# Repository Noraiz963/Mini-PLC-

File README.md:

# STM32 Mini PLC v1.0

A compact industrial-style PLC board designed in KiCad, built around an **STM32F407** microcontroller. It provides **8 optically isolated digital inputs**, **8 relay outputs**, **RS-485** communication and **USB-C** serial/bootloader access, all powered from **24 VDC**.

> **Status:** Hardware design v1.0 complete. The board has not been manufactured or tested, and no firmware has been written yet.

---

## Table of contents

- [Key features](#key-features)
- [Board gallery](#board-gallery)
- [Specifications](#specifications)
- [System overview](#system-overview)
- [Sub-systems](#sub-systems)
- [Connectors](#connectors)
- [PCB design](#pcb-design)
- [Repository structure](#repository-structure)
- [Project status and roadmap](#project-status-and-roadmap)
- [Tools](#tools)
- [License and credits](#license-and-credits)

---

## Key features

- STM32F407 microcontroller as the processing core
- 8 optically isolated digital inputs (optocoupler per channel)
- 8 relay outputs, MOSFET-driven, with freewheeling diodes
- RS-485 interface on a DB9 connector (suitable for Modbus RTU)
- USB-C with CH340C USB-to-UART bridge for serial debugging and bootloader flashing
- 5-pin SWD header for ST-LINK programming and debugging
- 24 VDC industrial supply with fuse and reverse-polarity protection
- Status LEDs on inputs and outputs
- Reset button

---

## Board gallery

### 3D render: top angle

### 3D render: side view

### 3D render: back side
Back side showing input labels (X1 to X8), copper routing and relay output pads.

### PCB layout (KiCad PCB editor)
Red traces are the top copper layer and blue traces are the bottom copper layer. The logic section (power, STM32, inputs, communication) is at the top, and the relay and output section is at the bottom.

---

## Specifications

| Parameter | Value |
|---|---|
| Microcontroller | STM32F407 |
| Supply input | 24 VDC |
| Digital inputs | 8, optically isolated |
| Relay outputs | 8, rated 250 VAC / 30 VDC, 5 A (per board silkscreen) |
| Communication | RS-485 (DB9 connector), USB-C (UART bridge) |
| Programming / debug | 5-pin SWD header for ST-LINK |
| Design tool | KiCad |
| Board layers | 2 (top and bottom copper) |
| Version | v1.0 |

---

## System overview

```mermaid
flowchart LR
    PWR[24 VDC input<br/>J1, F1, D1] --> BUCK[Buck converter U1]
    BUCK --> LDO[3.3 V regulator U2]
    LDO --> MCU[STM32F407<br/>U13]
    IN[Field inputs X1-X8<br/>J2] --> OPTO[Optocouplers<br/>U4-U11]
    OPTO --> MCU
    MCU --> FET[MOSFET drivers<br/>Q2-Q9]
    FET --> RLY[Relays K2-K9]
    RLY --> OUT[Outputs Y1-Y8<br/>J3]
    MCU <--> RS[RS-485 transceiver U12<br/>DB9 J4]
    MCU <--> USB[CH340C U14<br/>USB-C J19]
    MCU <--> SWD[SWD header J5]
```

---

## Sub-systems

| Sub-system | Key components | Description |
|---|---|---|
| Power stage | J1, F1, D1, U1, U2 | Accepts 24 VDC industrial input, protected by a fuse and a reverse-polarity diode. A switching buck converter (U1) and a 3.3 V linear regulator (U2) power the logic. |
| Processing core | U13 (STM32F407), C9 to C11 | Main microcontroller for application logic, with decoupling capacitors for stability. |
| Programming and debug | J5 (3V3, SWDIO, RST, SWCLK, GND) | 5-pin header for debugging and flashing with an external ST-LINK. Pin 1 is the 3.3 V reference (VTREF). |
| USB and serial | J19 (USB-C), U14 (CH340C) | USB-to-UART bridge for serial monitoring (printf debugging) and bootloader flashing. |
| Isolated digital inputs | J2, U4 to U11 (optocouplers) | 8 optically isolated channels that protect the STM32 from field-side voltage transients. |
| Relay output stage | K2 to K9, Q2 to Q9 (MOSFETs), D13 to D20, J3 | 8 electromechanical relays driven by MOSFET switches, with freewheeling diodes for inductive kickback protection. |
| Industrial communication | U12 (RS-485 transceiver), J4 | Differential serial interface for fieldbus networks. The hardware is suitable for Modbus RTU. |

---

## Connectors

| Ref | Function | Pins |
|---|---|---|
| J1 | 24 VDC power input | 24 V, 0 V |
| J2 | Digital inputs | X1 to X8, GND (see silkscreen) |
| J3 | Relay outputs | Y1 to Y8, plus common terminals (see silkscreen) |
| J4 | RS-485 (DB9) | Differential A/B, GND |
| J5 | SWD programming | 3V3, SWDIO, SWCLK, RST, GND |
| J19 | USB-C | UART bridge and bootloader |

---

## PCB design

- Logic section (power, MCU, optocoupled inputs, communication) kept separate from the relay section
- Relays placed along the bottom edge with output terminals on the same side
- Input terminal block along the top edge
- Mounting holes in all four corners
- Silkscreen labels for all terminals and ratings (Input: 24 V DC, Relay outputs: 250 VAC / 30 VDC, 5 A)

---

## Project status and roadmap

- [x] Schematic design
- [x] PCB layout
- [x] 3D model review
- [ ] Design rule check and final review
- [ ] Manufacture the board
- [ ] Write firmware
- [ ] Hardware testing

Specifications above come from the design, not from measurements on a built board.

---

## Tools

- KiCad (schematic, PCB layout, 3D viewer)

-

Designed by: *Noraiz*

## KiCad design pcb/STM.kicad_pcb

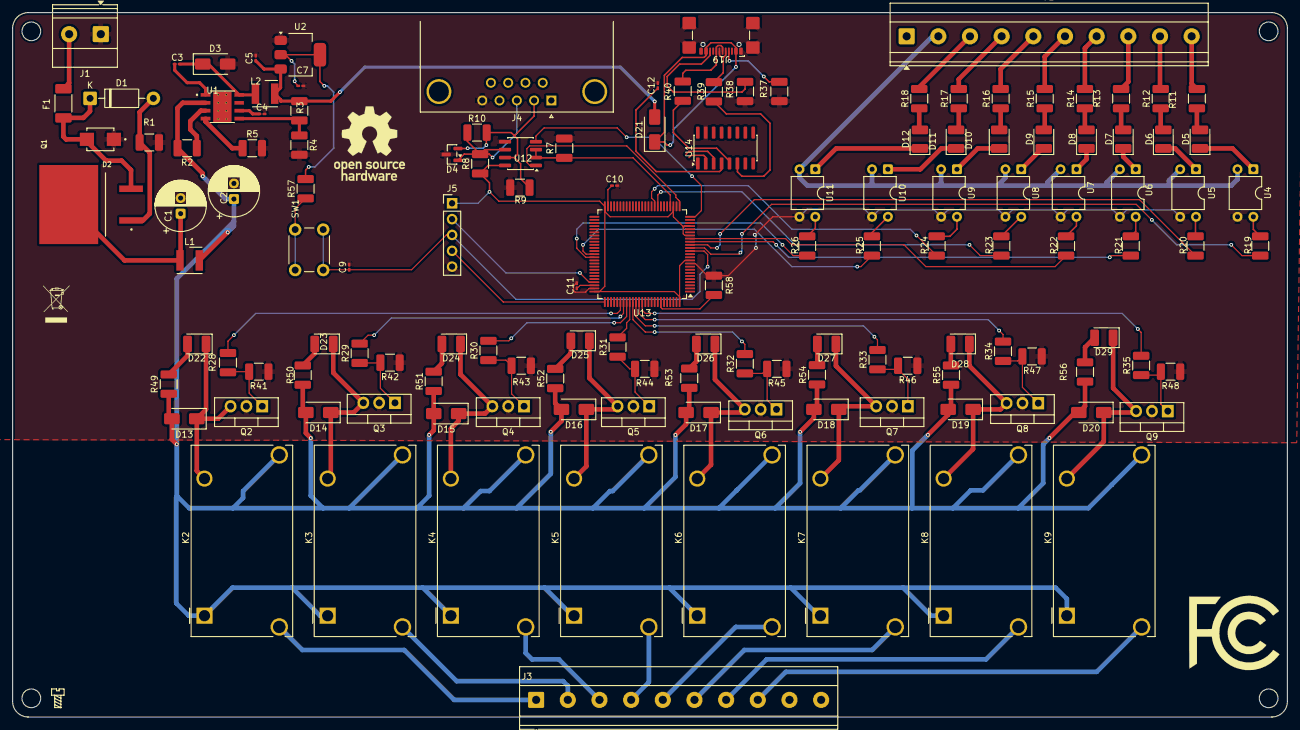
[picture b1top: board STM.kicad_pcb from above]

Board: 2 copper layers, 204.5 x 113.0 mm, 134 parts (0 on the bottom side), 117 nets.

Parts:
C1, C2: 47uF; CP_Radial_D8.0mm_P2.50mm
C3, C4, C9, C12: 100nF; C_0201_0603Metric_Pad0.64x0.40mm_HandSolder
C5: 47uF; C_0201_0603Metric_Pad0.64x0.40mm_HandSolder
C7: 15uF; C_0201_0603Metric_Pad0.64x0.40mm_HandSolder
C10, C11: 2.2uf; C_0201_0603Metric_Pad0.64x0.40mm_HandSolder
D1: 1N47xxA; D_DO-41_SOD81_P10.16mm_Horizontal
D2: SMBJ36A; DIOM4336X265N
D3, D21: SS34; D_SMA
D4: SM712_SOT23; SOT-23
D5, D6, D7, D8, D9, D10, D11, D12, D22, D23, D24, D25, D26, D27, D28, D29: LED; LED_1210_3225Metric_Pad1.42x2.65mm_HandSolder
D13, D14, D15, D16, D17, D18, D19, D20: SS14; D_SMA
F1: Fuse; Fuse_2010_5025Metric_Pad1.52x2.65mm_HandSolder
J1: Screw_Terminal_01x02; TerminalBlock_Phoenix_MKDS-1,5-2-5.08_1x02_P5.08mm_Horizont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
J2, J3: Screw_Terminal_01x10; TerminalBlock_Phoenix_MKDS-1,5-10-5.08_1x10_P5.08mm_Horizon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
J4: DE9_Pins; DSUB-9_Pins_Horizontal_P2.77x2.84mm_EdgePinOffset9.90mm_Hou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
J5: Conn_ARM_SWD_TagConnect_TC2030; PinHeader_1x05_P2.54mm_Vertical
J19: USB_C_Receptacle_USB2.0_16P; USB_C_Receptacle_GCT_USB4110
K2, K3, K4, K5, K6, K7, K8, K9: Panasonic_ALFG2PF241; Relay_SPST_Panasonic_ALFG_FormA_CircularHoles
L1: 10uH; L_Wurth_WE-LQSH-4020
L2: 15uH; L_Wurth_WE-LQSH-4020
Q1: FQB47P06TM-AM002; TO-263-3_ONSEMI
Q2, Q3, Q4, Q5, Q6, Q7, Q8, Q9: IRLZ44N; TO-220-3_Vertical
R1, R4, R7, R19, R20, R21, R22, R23, R24, R25, R26, R41, R42, R43, R44, R45, R46, R47, R48: 10K; R_1210_3225Metric_Pad1.30x2.65mm_HandSolder
R2, R5: 100K; R_1210_3225Metric_Pad1.30x2.65mm_HandSolder
R3: 52.3K; R_1210_3225Metric_Pad1.30x2.65mm_HandSolder
R8, R9: 1K; R_1210_3225Metric_Pad1.30x2.65mm_HandSolder
R10: 120; R_1210_3225Metric_Pad1.30x2.65mm_HandSolder
R11, R12, R13, R14, R15, R16, R17, R18, R49, R50, R51, R52, R53, R54, R55, R56: 4.7K; R_1210_3225Metric_Pad1.30x2.65mm_HandSolder
R28, R29, R30, R31, R32, R33, R34, R35: 10; R_1210_3225Metric_Pad1.30x2.65mm_HandSolder
R37, R38: 5.1K; R_1210_3225Metric_Pad1.30x2.65mm_HandSolder
R39, R40: 22; R_1210_3225Metric_Pad1.30x2.65mm_HandSolder
R57, R58: 10k; R_1210_3225Metric_Pad1.30x2.65mm_HandSolder
SW1: SW_Push; SW_PUSH_6mm
U1: LMR14030SDDA; VREG_LM5017MR_NOPB
U2: AMS1117-3.3; SOT-223-3_TabPin2
U4, U5, U6, U7, U8, U9, U10, U11: PC817; DIP-4_W7.62mm
U12: SP3485CN; SOIC-8_3.9x4.9mm_P1.27mm
U13: STM32F407VGTx; LQFP-100_14x14mm_P0.5mm
U14: CH340C; SOIC-16_3.9x9.9mm_P1.27mm

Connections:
/3.3V: C7.1, J5.1 (VCC), R8.1, R57.2, U2.2 (VO), U12.8 (VCC), U13.11 (VDD), U13.19 (VDD), U13.22 (VDDA), U13.28 (VDD), U13.50 (VDD), U13.75 (VDD), U13.100 (VDD), U14.16 (VCC)
/5v: C5.1, D21.2 (A), L2.2, R3.1, U2.3 (VI)
/24V: C2.1, D13.2 (A), D14.2 (A), D15.2 (A), D16.2 (A), D17.2 (A), D18.2 (A), D19.2 (A), D20.2 (A), K2.14, K2.A1, K3.14, K3.A1, K4.14, K4.A1, K5.14, K5.A1, K6.14, K6.A1, K7.14, K7.A1, K8.14, K8.A1, K9.14, K9.A1, L1.2, R2.2, R49.1, R50.1, R51.1, R52.1, R53.1, R54.1, R55.1, R56.1, U1.2 (VIN)
/A: D4.1 (A1), J4.3, R8.2, R10.1, U12.6 (A)
/B: D4.2 (A2), J4.2, R9.1, R10.2, U12.7 (B)
/GND1: J2.2, U4.2, U5.2, U6.2, U7.2, U8.2, U9.2, U10.2, U11.2
/I1: R19.1, U13.15 (PC0)
/I2: R20.1, U13.16 (PC1)
/I3: R21.1, U13.17 (PC2)
/I4: R22.1, U13.18 (PC3)
/I5: R23.1, U13.33 (PC4)
/I6: R24.1, U13.34 (PC5)
/I7: R25.1, U13.63 (PC6)
/I8: R26.1, U13.64 (PC7)
/O1: R28.2, U13.81 (PD0)
/O01: J3.1, K2.11
/O02: J3.2, K3.11
/O2: R29.2, U13.82 (PD1)
/O3: R30.2, U13.83 (PD2)
/O03: J3.3, K4.11
/O04: J3.4, K5.11
/O4: R31.2, U13.84 (PD3)
/O5: R32.2, U13.85 (PD4)
/O05: J3.5, K6.11
/O6: R33.2, U13.86 (PD5)
/O06: J3.6, K7.11
/O7: R34.2, U13.87 (PD6)
/O07: J3.7, K8.11
/O8: R35.2, U13.88 (PD7)
/O08: J3.8, K9.11
/RE/DE: R7.1, U12.2 (~RE), U12.3 (DE), U13.29 (PA4)
/RX: U13.69 (PA10), U14.2 (TXD)
/SWCLK: J5.4 (SWCLK), U13.76 (PA14)
/SWDIO: J5.2 (SWDIO), U13.72 (PA13)
/TX: U13.68 (PA9), U14.3 (RXD)
/USART2_RX: U12.1 (RO), U13.26 (PA3)
/USART2_TX: U12.4 (DI), U13.25 (PA2)
/reset: C9.1, J5.3 (~RESET), SW1.1, U13.14 (NRST)
GND: C1.2, C2.2, C4.2, C5.2, C7.2, C9.2, C10.2, C11.2, C12.2, D2.C, D3.2 (A), D4.3 (common), J1.1, J3.9, J4.5, J5.5 (GND), J19.A1 (GND), J19.A12 (GND), J19.B1 (GND), J19.B12 (GND), J19.SH (SHIELD), Q2.2 (D), Q3.2 (D), Q4.2 (D), Q5.2 (D), Q6.2 (D), Q7.2 (D), Q8.2 (D), Q9.2 (D), R1.2, R4.2, R5.2, R7.2, R9.2, R37.2, R38.2, R41.1, R42.1, R43.1, R44.1, R45.1, R46.1, R47.1, R48.1, R58.1, U1.7 (GND), U2.1 (GND), U4.3, U5.3, U6.3, U7.3, U8.3, U9.3, U10.3, U11.3, U12.5 (GND), U13.10 (VSS), U13.20 (VSSA), U13.27 (VSS), U13.74 (VSS), U13.99 (VSS), U14.1 (GND), U14.15 (R232)
unnamed: C1.1, L1.1, Q1.3
unnamed: D1.2 (A), Q1.1, R1.1
unnamed: D1.1 (K), D2.A, F1.2, Q1.2
unnamed: C3.2, D3.1 (K), L2.1, U1.8 (SW)
unnamed: D5.2 (A), R11.1
unnamed: D5.1 (K), U4.1
unnamed: D6.2 (A), R12.1
unnamed: D6.1 (K), U5.1
unnamed: D7.2 (A), R13.1
unnamed: D7.1 (K), U6.1
unnamed: D8.2 (A), R14.1
unnamed: D8.1 (K), U7.1
unnamed: D9.2 (A), R15.1
unnamed: D9.1 (K), U8.1
unnamed: D10.2 (A), R16.1
unnamed: D10.1 (K), U9.1
unnamed: D11.2 (A), R17.1
unnamed: D11.1 (K), U10.1
unnamed: D12.2 (A), R18.1
unnamed: D12.1 (K), U11.1
unnamed: D13.1 (K), D22.1 (K), K2.A2, Q2.3 (S)
unnamed: D14.1 (K), D23.1 (K), K3.A2, Q3.3 (S)
unnamed: D15.1 (K), D24.1 (K), K4.A2, Q4.3 (S)
unnamed: D16.1 (K), D25.1 (K), K5.A2, Q5.3 (S)
unnamed: D17.1 (K), D26.1 (K), K6.A2, Q6.3 (S)
unnamed: D18.1 (K), D27.1 (K), K7.A2, Q7.3 (S)
unnamed: D19.1 (K), D28.1 (K), K8.A2, Q8.3 (S)
unnamed: D20.1 (K), D29.1 (K), K9.A2, Q9.3 (S)
unnamed: D21.1 (K), J19.A4 (VBUS), J19.A9 (VBUS), J19.B4 (VBUS), J19.B9 (VBUS)
unnamed: D22.2 (A), R49.2
unnamed: D23.2 (A), R50.2
unnamed: D24.2 (A), R51.2
unnamed: D25.2 (A), R52.2
unnamed: D26.2 (A), R53.2
unnamed: D27.2 (A), R54.2
unnamed: D28.2 (A), R55.2
unnamed: D29.2 (A), R56.2
unnamed: F1.1, J1.2
unnamed: J2.3, R18.2
unnamed: J2.4, R17.2
unnamed: J2.5, R16.2
unnamed: J2.6, R15.2
unnamed: J2.7, R14.2
unnamed: J2.8, R13.2
unnamed: J2.9, R12.2
unnamed: J2.10, R11.2
unnamed: J19.A5 (CC1), R37.1
unnamed: J19.B5 (CC2), R38.1
unnamed: J19.A6 (D+), J19.B6 (D+), R40.1
unnamed: J19.A7 (D-), J19.B7 (D-), R39.1
unnamed: Q2.1 (G), R28.1, R41.2
unnamed: Q3.1 (G), R29.1, R42.2
unnamed: Q4.1 (G), R30.1, R43.2
unnamed: Q5.1 (G), R31.1, R44.2
unnamed: Q6.1 (G), R32.1, R45.2
unnamed: Q7.1 (G), R33.1, R46.2
unnamed: Q8.1 (G), R34.1, R47.2
unnamed: Q9.1 (G), R35.1, R48.2
unnamed: R19.2, U4.4
unnamed: R20.2, U5.4
unnamed: R21.2, U6.4
unnamed: R22.2, U7.4
unnamed: R23.2, U8.4
unnamed: R24.2, U9.4
unnamed: R25.2, U10.4
unnamed: R26.2, U11.4
unnamed: R57.1, SW1.2
unnamed: C3.1, U1.1 (BOOT)
unnamed: R2.1, U1.3 (EN)
unnamed: R3.2, R4.1, U1.5 (FB)
unnamed: R5.1, U1.4 (RT/SYNC)
unnamed: C4.1, U1.6 (SS)
unnamed: R58.2, U13.94 (BOOT0)
unnamed: C10.1, U13.49 (VCAP_1)
unnamed: C11.1, U13.73 (VCAP_2)
unnamed: R40.2, U14.5 (UD+)
unnamed: R39.2, U14.6 (UD-)
unnamed: C12.1, U14.4 (V3)
